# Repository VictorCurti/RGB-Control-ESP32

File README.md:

# RGB Control ESP32 by Victor Curti

# Application

## :page_with_curl: About :

This IOT project aims to control an RGB LED strip (SMD 5050) using Wifi network to communicate the aplication uising HTML5 or Alex voice comande, for this project the ESP32 DevKit V1 was chosen as a controller.

## :selfie: Interfaces :
<table>
  <tr>
    <td>HTML</td>
     <td>BLynk</td>
     
  </tr>
    <td></td>
 
 </table>
 
Was possible to acess webpage using any browser using as url:
```
  <IP_ADRRES.localhost:8080>

```

# Circuit 

## Schematic:

Full schematic: https://github.com/VictorCurti/RGB-Control-ESP32/blob/main/Kicad/RGB_Control.pdf

### Driver:

### Controller :

### Supply:

## PCB:

|   |  |
| ----------------------------------------------------- | ---------------------------------------------------- |
|   |  |

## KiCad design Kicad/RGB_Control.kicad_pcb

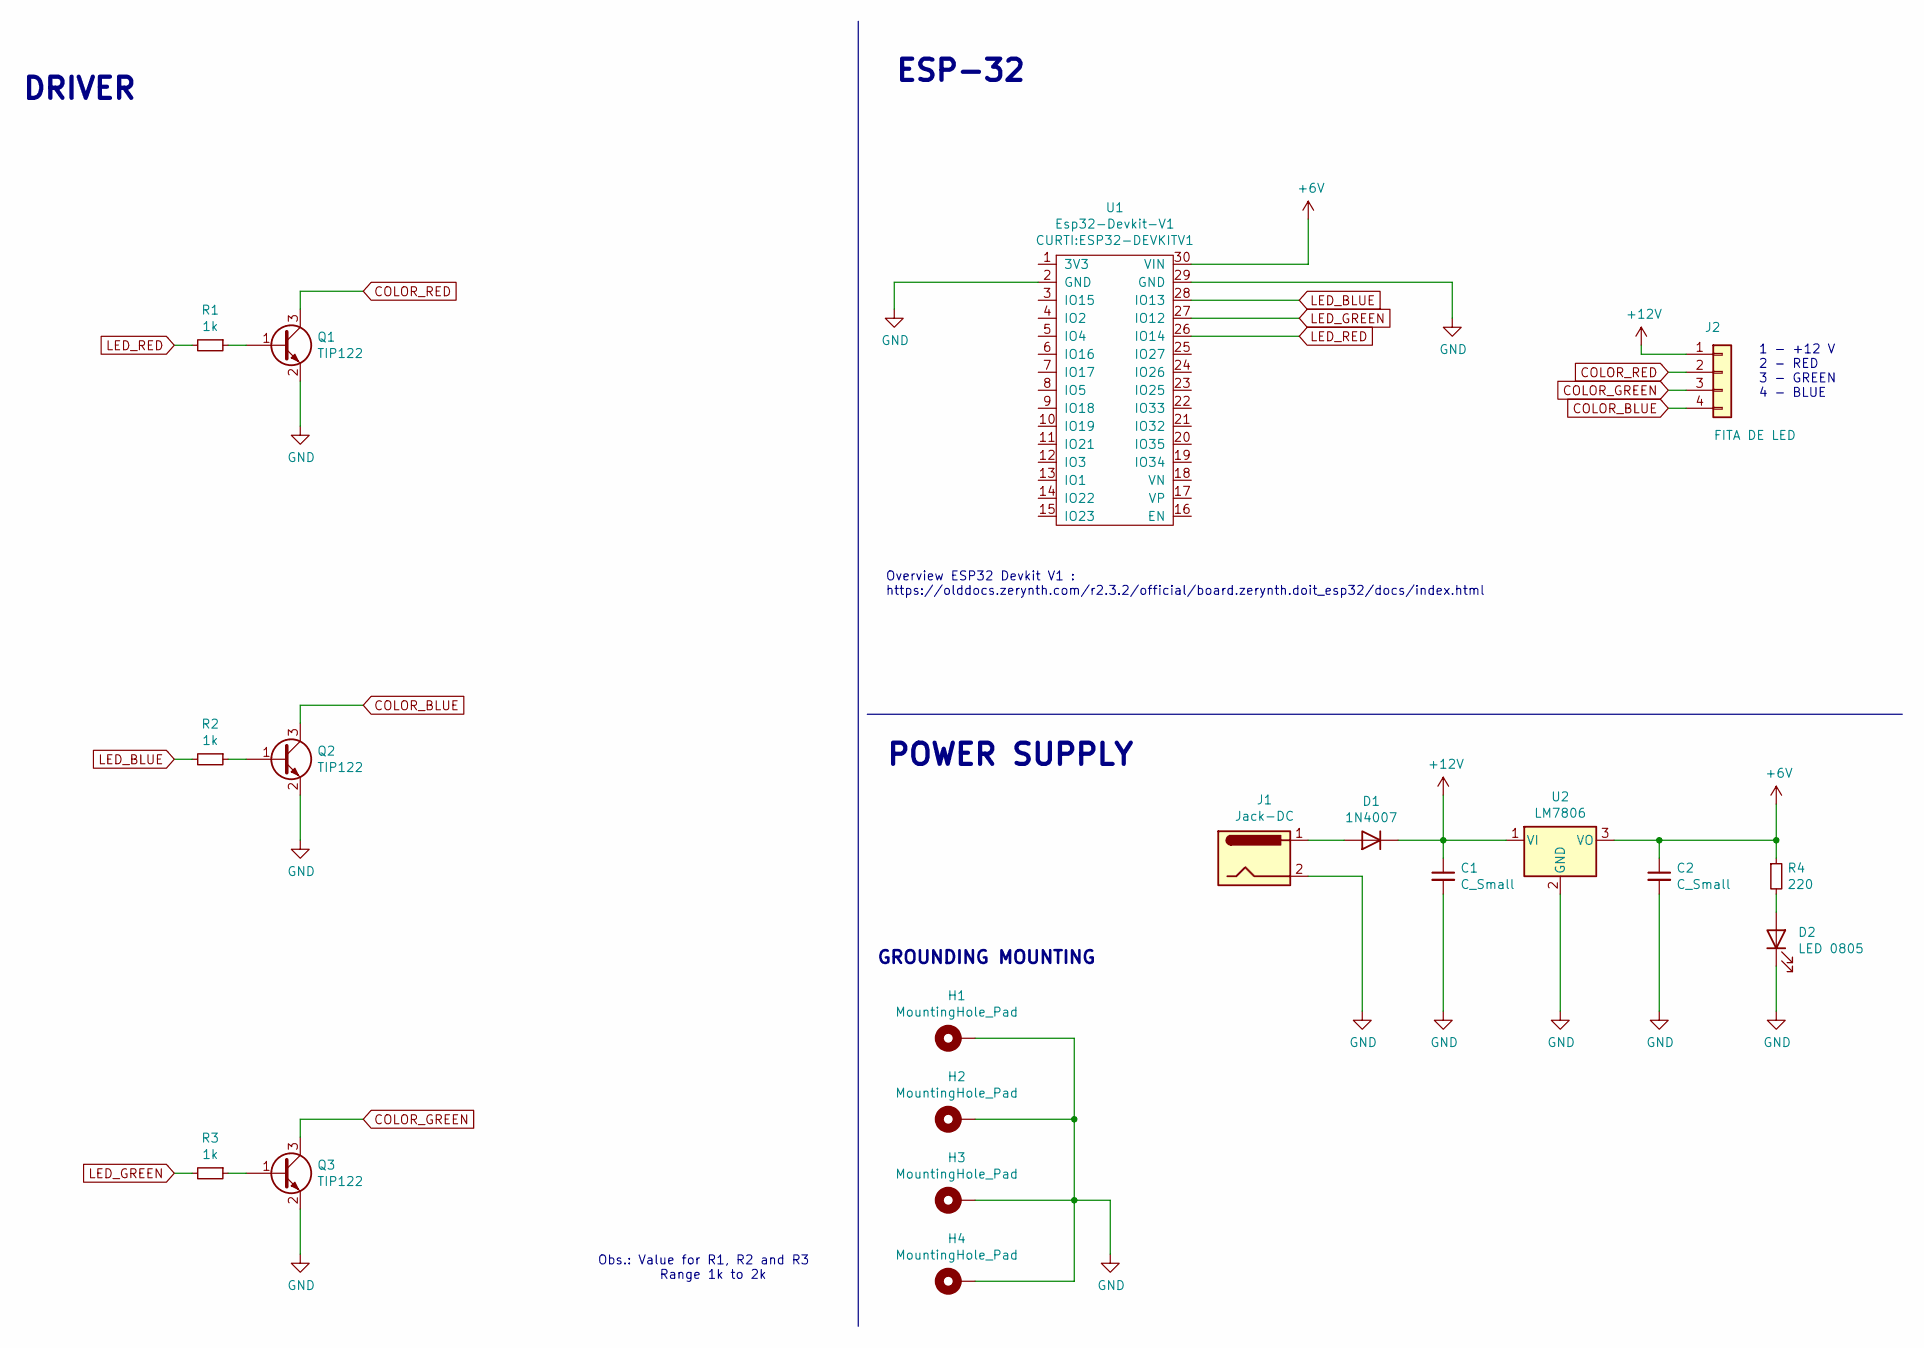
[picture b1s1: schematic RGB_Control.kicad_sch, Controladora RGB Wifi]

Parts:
C1, C2: C_Small; C_Rect_L4.6mm_W2.0mm_P2.50mm_MKS02_FKP02
D1: 1N4007; D_A-405_P2.54mm_Vertical_AnodeUp
D2: LED 0805; LED_D3.0mm
H1, H2, H3, H4: MountingHole_Pad; MountingHole_2.2mm_M2_Pad_Via
J1: Jack-DC; SolderWire-0.25sqmm_1x02_P4.2mm_D0.65mm_OD1.7mm
J2: FITA DE LED; PinHeader_1x04_P2.54mm_Vertical
Q1, Q2, Q3: TIP122; TO-220-3_Horizontal_TabDown
R1, R2, R3: 1k; R_Axial_DIN0207_L6.3mm_D2.5mm_P7.62mm_Horizontal
R4: 220; R_Axial_DIN0207_L6.3mm_D2.5mm_P2.54mm_Vertical
U1: Esp32-Devkit-V1; ESP32-DEVKITV1
U2: LM7806; TO-220-3_Vertical

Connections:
+6V: C2.1, R4.1, U1.30 (VIN), U2.3 (VO); also elsewhere on the board
+12V: C1.1, D1.1 (K), J2.1, U2.1 (VI)
COLOR_BLUE: J2.4, Q2.3 (C)
COLOR_GREEN: J2.3, Q3.3 (C)
COLOR_RED: J2.2, Q1.3 (C)
GND: C1.2, C2.2, D2.1 (K), H1.1, H2.1, H3.1, H4.1, J1.2, Q1.2 (E), Q2.2 (E), Q3.2 (E), U1.2 (GND), U1.29 (GND), U2.2 (GND)
LED_BLUE: R2.2, U1.28 (IO13)
LED_GREEN: R3.2, U1.27 (IO12)
LED_RED: R1.2, U1.26 (IO14)
unnamed: D1.2 (A), J1.1
unnamed 10: D2.2 (A), R4.2; also elsewhere on the board
unnamed: Q1.1 (B), R1.1
unnamed: Q2.1 (B), R2.1
unnamed: Q3.1 (B), R3.1

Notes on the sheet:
Overview ESP32 Devkit V1 : https://olddocs.zerynth.com/r2.3.2/official/board.zerynth.doit_esp32/docs/index.html
DRIVER
Obs.: Value for R1, R2 and R3 Range 1k to 2k
GROUNDING MOUNTING
ESP-32
POWER SUPPLY
1 - +12 V 2 - RED 3 - GREEN 4 - BLUE

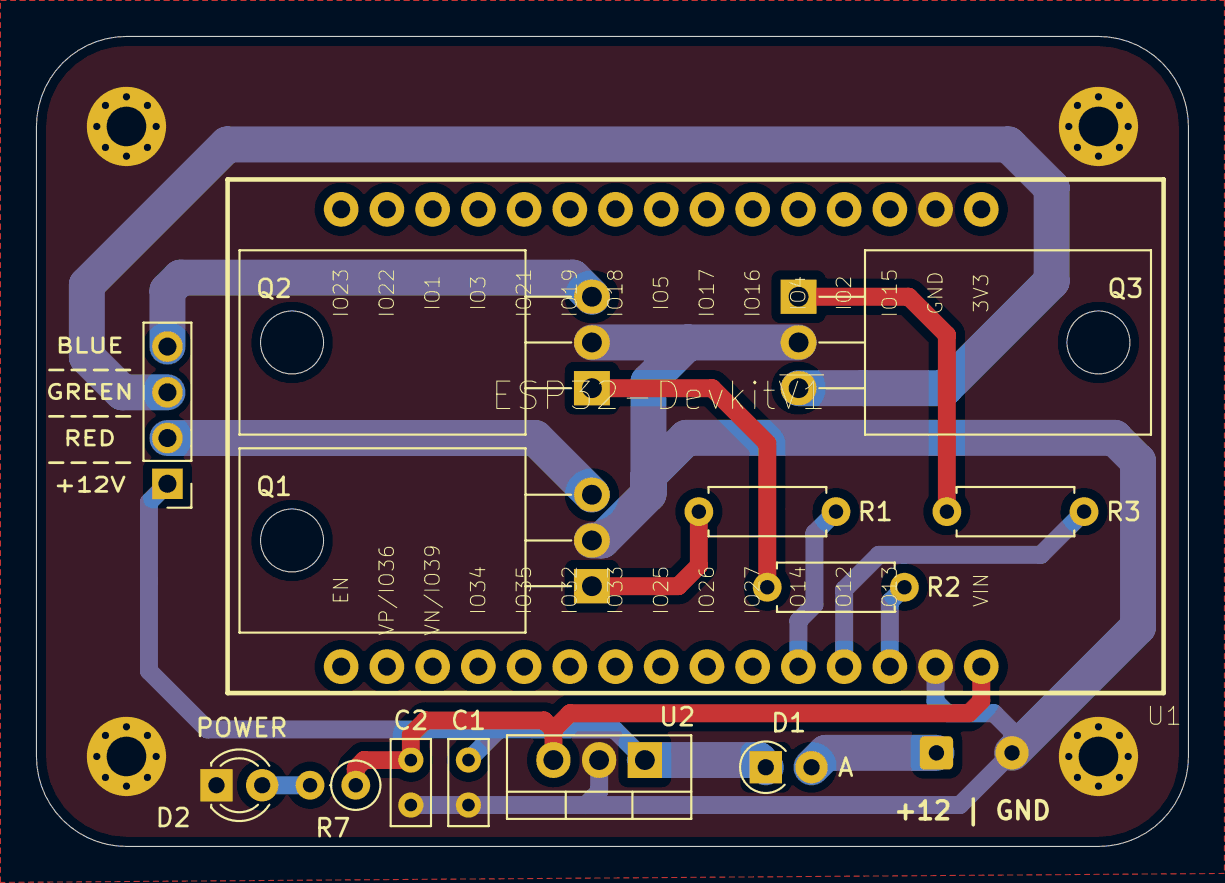
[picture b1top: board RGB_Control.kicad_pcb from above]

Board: 2 copper layers, 64.0 x 45.0 mm, 19 parts (0 on the bottom side), 14 nets.

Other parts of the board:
R7: 220; R_Axial_DIN0207_L6.3mm_D2.5mm_P2.54mm_Vertical

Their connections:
+6V: R7.1; also elsewhere on the board
unnamed 10: R7.2; also elsewhere on the board

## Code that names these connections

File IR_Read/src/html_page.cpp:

#include <Arduino.h>
#ifdef ESP32
#include <WiFi.h>
#include <AsyncTCP.h>
#else
#include <ESP8266WiFi.h>
#include <ESPAsyncTCP.h>
#endif
#include <ESPAsyncWebServer.h>
#include "HTML_Index.h"
#include <map>

AsyncWebServer server(80);

// Maping pins
#define LED_RED 14
#define LED_GREEN 12
#define LED_BLUE 13

// PWM CONFIGURATION
#define ChannelPwmRed 0
#define ChannelPwmGreen 1
#define ChannelPwmBlue 2
#define FrequencyPwm 60 //Hz

int FadeDelay;
int StrobeDelay;

// Wifi
const char *ssid = "Free_Internet_Discada";
const char *password = "ManelBixo";

// Tag comunication
const char *PARAM_INPUT_1 = "color";
const char *PARAM_INPUT_2 = "power";
const char *PARAM_INPUT_3 = "mode";
const char *PARAM_INPUT_4 = "intensity";
const char *PARAM_INPUT_5 = "speed";

String Power = "OFF", Mode = "NULL", Color = "#000000";
int intensity = 128;
int Fade_Red, Fade_Green, Fade_Blue, Fade_Step;

struct RGB_Color
{
  int Red = 0; //RGB code color
  //int PwmRed = map(Red, 0, 255, 0, 1023);     //Conversion RGB (8 bits) to PWM (10 bits)
  int Green = 0; //RGB code color
  //int PwmGreen = map(Green, 0, 255, 0, 1023); //Conversion RGB (8 bits) to PWM (10 bits)
  int Blue = 0; //RGB code color
  //int PwmBlue = map(Blue, 0, 255, 0, 1023);   //Conversion RGB (8 bits) to PWM (10 bits)
} Cor_RGB;

/**************************/
std::map<char, int> HexTable;

void Init_Map();

RGB_Color Cor;

void notFound(AsyncWebServerRequest *request);
void Hex2RGB(String HEX_COLOR);
void SerialDebug();
void PWM_RGB();

void setup()
{
  Init_Map();

  pinMode(LED_RED, OUTPUT);
  pinMode(LED_GREEN, OUTPUT);
  pinMode(LED_BLUE, OUTPUT);

  digitalWrite(LED_RED, HIGH);
  digitalWrite(LED_GREEN, HIGH);
  digitalWrite(LED_BLUE, HIGH);

  Serial.begin(115200);
  WiFi.mode(WIFI_STA);
  WiFi.begin(ssid, password);

  if (WiFi.waitForConnectResult() != WL_CONNECTED)
  {
    Serial.println("WiFi Failed!");
    return;
  }

  Serial.println();
  Serial.print("IP Address: ");
  Serial.println(WiFi.localIP());

  // Send web page with input fields to client
  server.on("/", HTTP_GET, [](AsyncWebServerRequest *request) {
    request->send_P(200, "text/html", index_html);
  });

  server.on("/get", HTTP_GET, [](AsyncWebServerRequest *request) {
    if (request->hasParam(PARAM_INPUT_1))
    {
      (request->getParam(PARAM_INPUT_1)->value()) == "" ? Color = "000000" : Color = request->getParam(PARAM_INPUT_1)->value();
      Mode = "Color";
      Power = "ON";
      Hex2RGB(Color);
    }
    else if (request->hasParam(PARAM_INPUT_2))
    {
      Power = request->getParam(PARAM_INPUT_2)->value();
    }
    else if (request->hasParam(PARAM_INPUT_3))
    {
      Mode = request->getParam(PARAM_INPUT_3)->value();
      Power = "ON";
      Fade_Red = 0;
      Fade_Green = 0;
      Fade_Blue = 0;
      Fade_Step = 0;
      randomSeed(analogRead(5));

      FadeDelay = 20;
      StrobeDelay = 200;
    }
    else if (request->hasParam(PARAM_INPUT_4))
    {
      if (request->getParam(PARAM_INPUT_4)->value() == "up")
      {
        intensity += 10;
        if (intensity > 256)
          intensity = 256;
      }
      else if (request->getParam(PARAM_INPUT_4)->value() == "down")
      {
        intensity -= 10;
        if (intensity < 0)
          intensity = 0;
      }
    }
    else if (request->hasParam(PARAM_INPUT_5))
    {
      if (request->getParam(PARAM_INPUT_5)->value() == "up")
      {
        FadeDelay++;
        StrobeDelay += 20;
      }
      else if (request->getParam(PARAM_INPUT_5)->value() == "down")
      {
        FadeDelay--;
        StrobeDelay -= 20;
      }
    }

    request->redirect("/"); // (/?color=FFFFFF)
  });

  server.on("/reset", HTTP_GET, [](AsyncWebServerRequest *request) {
    request->send_P(200, "text/html", "ESP rebooting now");
    delay(500);
    request->redirect("/");
    ESP.restart();
  });

  server.onNotFound(notFound);
  server.begin();

  /***** PWM CONFIGURATION *******/
  ledcSetup(ChannelPwmRed, FrequencyPwm, 8);
  ledcSetup(ChannelPwmGreen, FrequencyPwm, 8);
  ledcSetup(ChannelPwmBlue, FrequencyPwm, 8);

  /***** PWM CHANEL *******/
  ledcAttachPin(LED_RED, ChannelPwmRed);
  ledcAttachPin(LED_GREEN, ChannelPwmGreen);
  ledcAttachPin(LED_BLUE, ChannelPwmBlue);
}

void loop()
{
  SerialDebug();

  PWM_RGB();
}

void notFound(AsyncWebServerRequest *request)
{
  request->send(404, "text/plain", "404 - Not found");
}

void Hex2RGB(String HEX_COLOR)
{
  Cor_RGB.Red = (HexTable[HEX_COLOR[1]] * 16 + HexTable[HEX_COLOR[2]]);
  Cor_RGB.Green = (HexTable[HEX_COLOR[3]] * 16 + HexTable[HEX_COLOR[4]]);
  Cor_RGB.Blue = (HexTable[HEX_COLOR[5]] * 16 + HexTable[HEX_COLOR[6]]);
}

void Init_Map()
{
  HexTable['0'] = 0;
  HexTable['1'] = 1;
  HexTable['2'] = 2;
  HexTable['3'] = 3;
  HexTable['4'] = 4;
  HexTable['5'] = 5;
  HexTable['6'] = 6;
  HexTable['7'] = 7;
  HexTable['8'] = 8;
  HexTable['9'] = 9;
  HexTable['a'] = 10;
  HexTable['b'] = 11;
  HexTable['c'] = 12;
  HexTable['d'] = 13;
  HexTable['e'] = 14;
  HexTable['f'] = 15;
}

long OldTime = -1;
void SerialDebug()
{
  if ((OldTime == -1) || ((millis() - OldTime) >= 1000))
  {
    OldTime = millis();
    Serial.println("Mensagens:");
    Serial.print("\tPower: ");
    Serial.println(Power);
    Serial.print("\tColor: ");
    Serial.println(Color);
    Serial.print("\t\tRED: ");
    Serial.println(Cor_RGB.Red);
    Serial.print("\t\tGREEN: ");
    Serial.println(Cor_RGB.Green);
    Serial.print("\t\tBLUE: ");
    Serial.println(Cor_RGB.Blue);

    Serial.print("\t\tFADE - RED: ");
    Serial.println(Fade_Red);
    Serial.print("\t\tFADE - GREEN: ");
    Serial.println(Fade_Green);
    Serial.print("\t\tFADE - BLUE: ");
    Serial.println(Fade_Blue);
    Serial.print("\t\tFADE - STEP: ");
    Serial.println(Fade_Step);

    Serial.print("\tMode: ");
    Serial.println(Mode);
    Serial.print("\tIntensity: ");
    Serial.println(intensity);
  }
}

void PWM_RGB()
{
  if (Power == "ON" && Mode == "Color")
  {
    ledcWrite(0, (256 - Cor_RGB.Red));
    ledcWrite(1, (256 - Cor_RGB.Green));
    ledcWrite(2, (256 - Cor_RGB.Blue));
    delay(100);
  }
  else if (Power == "ON" && Mode == "Fade")
  {
    ledcWrite(0, (256 - Fade_Red));
    ledcWrite(1, (256 - Fade_Green));
    ledcWrite(2, (256 - Fade_Blue));

    if (Fade_Step == 0 && Fade_Red < 256)
      Fade_Red++;
    else if (Fade_Step == 1 && Fade_Green < 256)
      Fade_Green++;
    else if (Fade_Step == 2 && Fade_Blue < 256)
      Fade_Blue++;
    else if (Fade_Step == 3 && Fade_Red > 0)
      Fade_Red--;
    else if (Fade_Step == 4 && Fade_Green > 0)
      Fade_Green--;
    else if (Fade_Step == 5 && Fade_Blue > 0)
      Fade_Blue--;

    if (Fade_Red == 256 && Fade_Step == 0)
      Fade_Step++;
    else if (Fade_Green == 256 && Fade_Step == 1)
      Fade_Step++;
    else if (Fade_Blue == 256 && Fade_Step == 2)
      Fade_Step++;
    else if (Fade_Red == 0 && Fade_Step == 3)
      Fade_Step++;
    else if (Fade_Green == 0 && Fade_Step == 4)
      Fade_Step++;
    else if (Fade_Blue == 0 && Fade_Step == 5)
      Fade_Step = 0;

    delay(FadeDelay);
  }
  else if (Power == "ON" && Mode == "Strobe")
  {

    ledcWrite(0, 256);
    ledcWrite(1, 256);
    ledcWrite(2, 256);

    switch (random(0, 7))
    {
    case 0:
      ledcWrite(0, (256 - random(30, intensity)));
      break;
    case 1:
      ledcWrite(1, (256 - random(30, intensity)));
      break;
    case 2:
      ledcWrite(2, (256 - random(30, intensity)));
      break;
    case 3:
      ledcWrite(0, (256 - random(30, intensity)));
      ledcWrite(1, (256 - random(30, intensity)));
      break;
    case 4:
      ledcWrite(0, (256 - random(30, intensity)));
      ledcWrite(2, (256 - random(30, intensity)));
      break;
    case 5:
      ledcWrite(1, (256 - random(30, intensity)));
      ledcWrite(2, (256 - random(30, intensity)));
      break;
    case 6:
      ledcWrite(0, (256 - random(30, intensity)));
      ledcWrite(1, (256 - random(30, intensity)));
      ledcWrite(2, (256 - random(30, intensity)));
      break;
    default:
      ledcWrite(0, 256);
      ledcWrite(1, 256);
      ledcWrite(2, 256);
    }

    delay(StrobeDelay);
  }
  else if (Power == "OFF")
  {
    ledcWrite(0, 256);
    ledcWrite(1, 256);
    ledcWrite(2, 256);
  }
}

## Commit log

2021-04-08 Main
2021-04-20 Blynk + HTML
2021-04-27 Backup
2021-04-27 IR Read Remove
2021-04-27 Clean
2021-04-27 code correction
2021-04-27 .vscode remove
2021-04-27 Clear
2021-04-27 commit message
2021-05-05 Image Updade
2021-05-05 QrCode Blynk Clone Project
2021-05-05 Blynk screenshots
2021-05-06 Kicad PCB
2021-05-07 Schematic Imagens
2021-05-26 Alexa Update
2021-05-26 Credentials
2021-05-27 Circuit V2 - BJT
2022-07-02 fix Espalexa.h and ESPAsyncWebServer.h
2022-07-03 Fix & update
2022-07-09 add auto wifi reconnect
2022-09-20 Fix Wifi
2022-09-27 Fix readme
